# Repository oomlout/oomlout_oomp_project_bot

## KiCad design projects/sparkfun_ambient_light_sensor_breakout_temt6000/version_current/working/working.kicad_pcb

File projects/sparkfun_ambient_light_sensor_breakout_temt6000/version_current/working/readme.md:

# OOMP Project  
## Ambient_Light_Sensor_Breakout-TEMT6000  by sparkfun  
  
oomp key: oomp_projects_flat_sparkfun_ambient_light_sensor_breakout_temt6000  
(snippet of original readme)  
  
SparkFun Ambient Light Sensor Breakout Board - TEMT6000  
=========================================================  

[*SparkFun Ambient Light Sensor Breakout Board - TEMT6000 (BOB-08688)*](https://www.sparkfun.com/products/8688)  
  
 Basic breakout board for the TEMT6000 Ambient Light Sensor.  

Repository Contents  
-------------------  
  
* **/Hardware** - All Eagle design files (.brd, .sch)  
  
Documentation  
--------------  
  
* **[Hookup Guide](https://learn.sparkfun.com/tutorials/temt6000-ambient-light-sensor-hookup-guide)** - Basic hookup guide.  
  
License Information  
-------------------  
The hardware is released under [Creative Commons ShareAlike 4.0 International](https://creativecommons.org/licenses/by-sa/4.0/).  
  
Distributed as-is; no warranty is given.  
  
  full source readme at [readme_src.md](readme_src.md)  
  
source repo at: [https://github.com/sparkfun/Ambient_Light_Sensor_Breakout-TEMT6000](https://github.com/sparkfun/Ambient_Light_Sensor_Breakout-TEMT6000)  
## Board  

## Schematic  

[schematic pdf](working_schematic.pdf)  
## Images

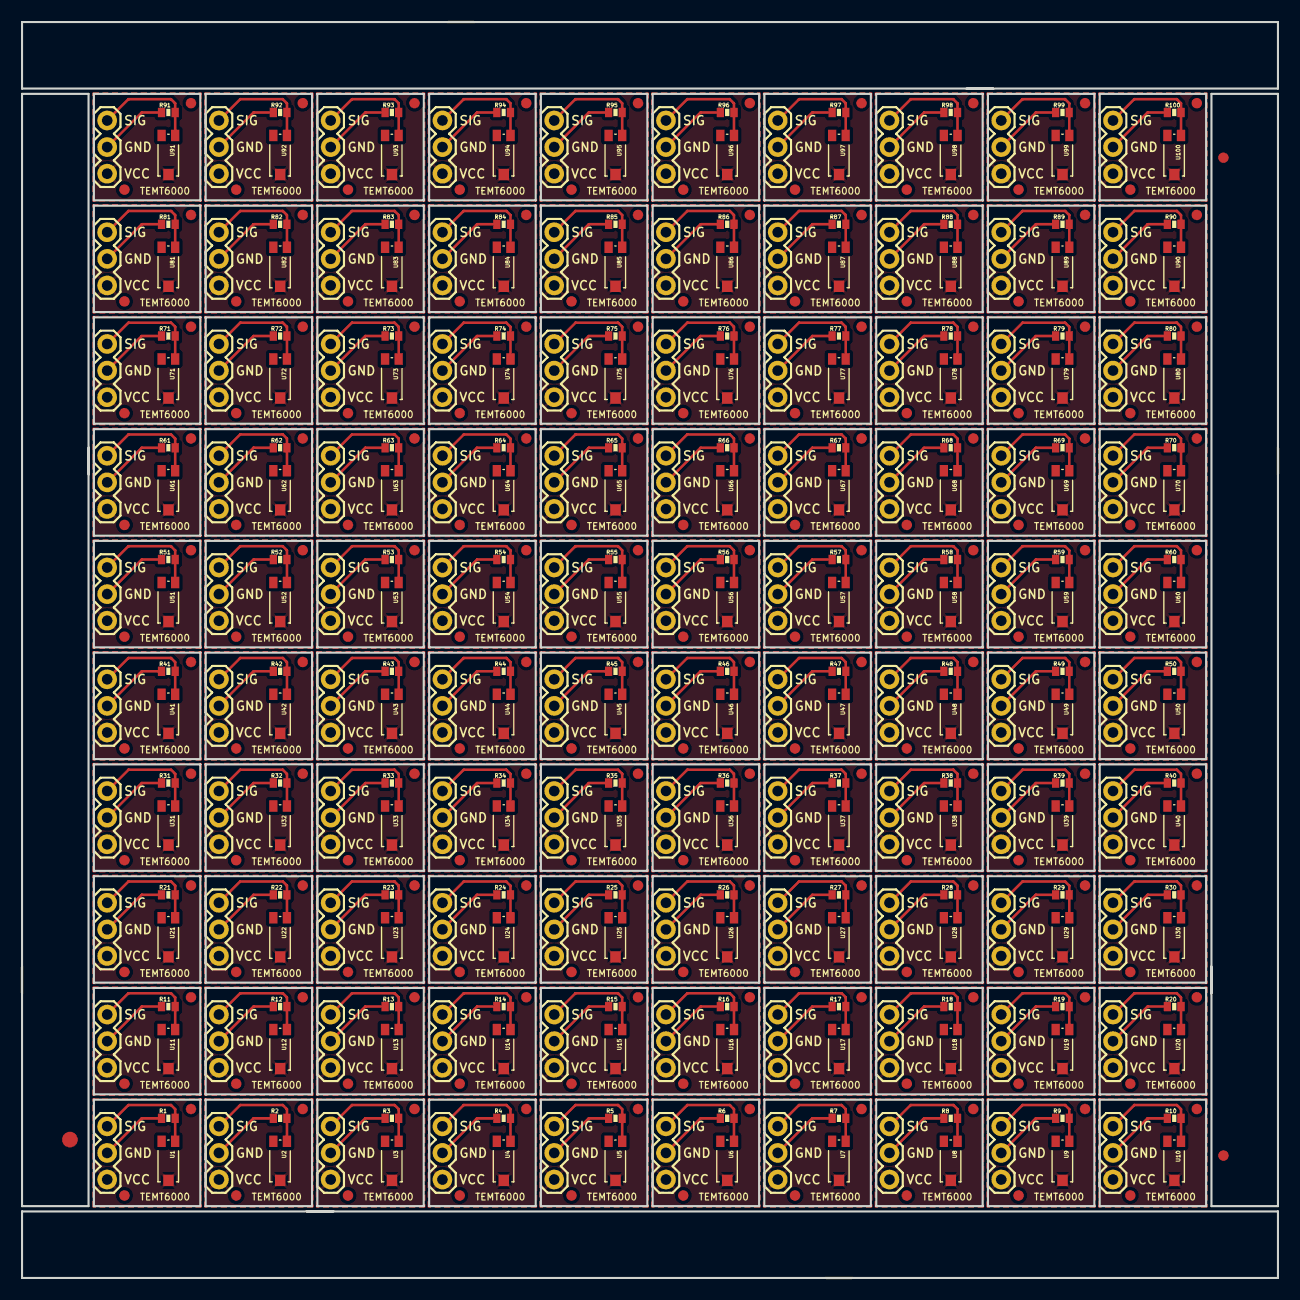
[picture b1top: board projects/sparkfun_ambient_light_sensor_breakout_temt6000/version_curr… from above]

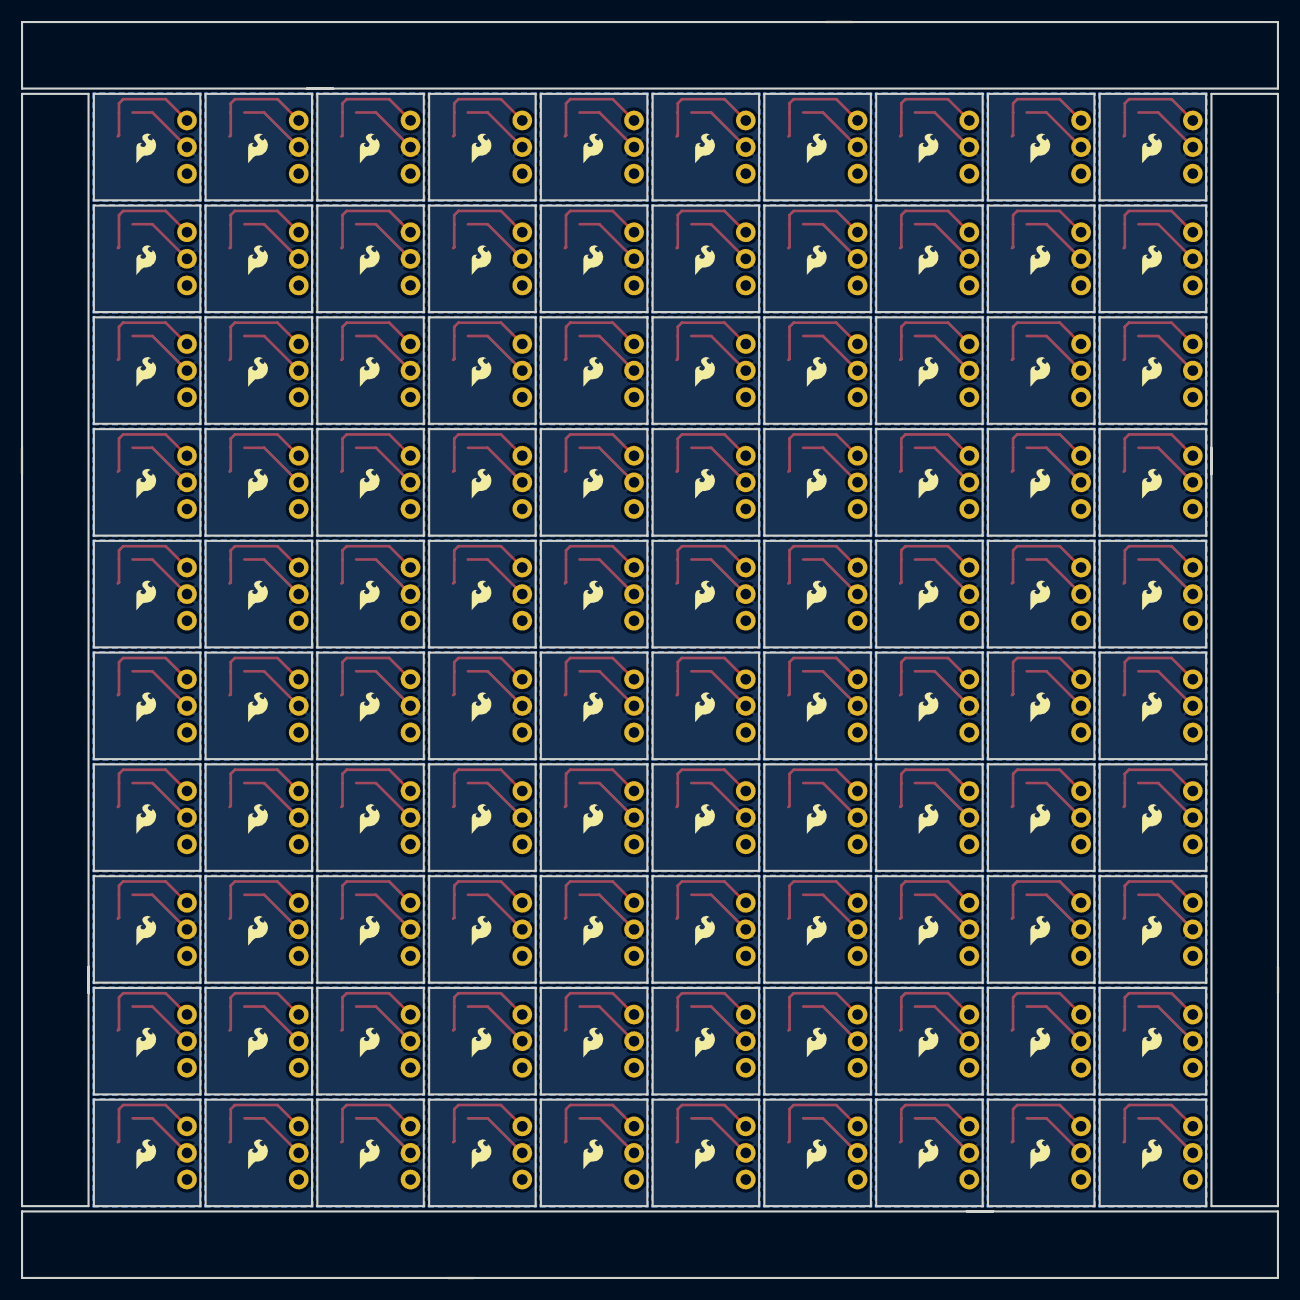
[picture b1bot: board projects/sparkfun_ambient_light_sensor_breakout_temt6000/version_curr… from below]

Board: 16 copper layers, 119.9 x 119.9 mm, 603 parts (100 on the bottom side), 300 nets.

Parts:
E$1, E$2, E$3, E$4, E$5, E$6, E$7, E$8, E$9, E$10, E$11, E$12, E$13, E$14, E$15, E$16, E$17, E$18, E$19, E$20, E$21, E$22, E$23, E$24, E$25, E$26, E$27, E$28, E$29, E$30, E$31, E$32, E$33, E$34, E$35, E$36, E$37, E$38, E$39, E$40, E$41, E$42, E$43, E$44, E$45, E$46, E$47, E$48, E$49, E$50, E$51, E$52, E$53, E$54, E$55, E$56, E$57, E$58, E$59, E$60, E$61, E$62, E$63, E$64, E$65, E$66, E$67, E$68, E$69, E$70, E$71, E$72, E$73, E$74, E$75, E$76, E$77, E$78, E$79, E$80, E$81, E$82, E$83, E$84, E$85, E$86, E$87, E$88, E$89, E$90, E$91, E$92, E$93, E$94, E$95, E$96, E$97, E$98, E$99, E$100, E$101, E$102, E$103, E$104, E$105, E$106, E$107, E$108, E$109, E$110, E$111, E$112, E$113, E$114, E$115, E$116, E$117, E$118, E$119, E$120, E$121, E$122, E$123, E$124, E$125, E$126, E$127, E$128, E$129, E$130, E$131, E$132, E$133, E$134, E$135, E$136, E$137, E$138, E$139, E$140, E$141, E$142, E$143, E$144, E$145, E$146, E$147, E$148, E$149, E$150, E$151, E$152, E$153, E$154, E$155, E$156, E$157, E$158, E$159, E$160, E$161, E$162, E$163, E$164, E$165, E$166, E$167, E$168, E$169, E$170, E$171, E$172, E$173, E$174, E$175, E$176, E$177, E$178, E$179, E$180, E$181, E$182, E$183, E$184, E$185, E$186, E$187, E$188, E$189, E$190, E$191, E$192, E$193, E$194, E$195, E$196, E$197, E$198, E$199, E$200, E$205, E$206: FIDUCIAL-1X2
E$201: FIDUCIAL-1.5X3
JP1, JP2, JP3, JP4, JP5, JP6, JP7, JP8, JP9, JP10, JP11, JP12, JP13, JP14, JP15, JP16, JP17, JP18, JP19, JP20, JP21, JP22, JP23, JP24, JP25, JP26, JP27, JP28, JP29, JP30, JP31, JP32, JP33, JP34, JP35, JP36, JP37, JP38, JP39, JP40, JP41, JP42, JP43, JP44, JP45, JP46, JP47, JP48, JP49, JP50, JP51, JP52, JP53, JP54, JP55, JP56, JP57, JP58, JP59, JP60, JP61, JP62, JP63, JP64, JP65, JP66, JP67, JP68, JP69, JP70, JP71, JP72, JP73, JP74, JP75, JP76, JP77, JP78, JP79, JP80, JP81, JP82, JP83, JP84, JP85, JP86, JP87, JP88, JP89, JP90, JP91, JP92, JP93, JP94, JP95, JP96, JP97, JP98, JP99, JP100: 1X03
R1, R2, R3, R4, R5, R6, R7, R8, R9, R10, R11, R12, R13, R14, R15, R16, R17, R18, R19, R20, R21, R22, R23, R24, R25, R26, R27, R28, R29, R30, R31, R32, R33, R34, R35, R36, R37, R38, R39, R40, R41, R42, R43, R44, R45, R46, R47, R48, R49, R50, R51, R52, R53, R54, R55, R56, R57, R58, R59, R60, R61, R62, R63, R64, R65, R66, R67, R68, R69, R70, R71, R72, R73, R74, R75, R76, R77, R78, R79, R80, R81, R82, R83, R84, R85, R86, R87, R88, R89, R90, R91, R92, R93, R94, R95, R96, R97, R98, R99, R100: 10K; 0402-RES
U1, U2, U3, U4, U5, U6, U7, U8, U9, U10, U11, U12, U13, U14, U15, U16, U17, U18, U19, U20, U21, U22, U23, U24, U25, U26, U27, U28, U29, U30, U31, U32, U33, U34, U35, U36, U37, U38, U39, U40, U41, U42, U43, U44, U45, U46, U47, U48, U49, U50, U51, U52, U53, U54, U55, U56, U57, U58, U59, U60, U61, U62, U63, U64, U65, U66, U67, U68, U69, U70, U71, U72, U73, U74, U75, U76, U77, U78, U79, U80, U81, U82, U83, U84, U85, U86, U87, U88, U89, U90, U91, U92, U93, U94, U95, U96, U97, U98, U99, U100: TEMT6000; TEMT6000-SEN
U$1, U$2, U$3, U$4, U$5, U$6, U$7, U$8, U$9, U$10, U$11, U$12, U$13, U$14, U$15, U$16, U$17, U$18, U$19, U$20, U$21, U$22, U$23, U$24, U$25, U$26, U$27, U$28, U$29, U$30, U$31, U$32, U$33, U$34, U$35, U$36, U$37, U$38, U$39, U$40, U$41, U$42, U$43, U$44, U$45, U$46, U$47, U$48, U$49, U$50, U$51, U$52, U$53, U$54, U$55, U$56, U$57, U$58, U$59, U$60, U$61, U$62, U$63, U$64, U$65, U$66, U$67, U$68, U$69, U$70, U$71, U$72, U$73, U$74, U$75, U$76, U$77, U$78, U$79, U$80, U$81, U$82, U$83, U$84, U$85, U$86, U$87, U$88, U$89, U$90, U$91, U$92, U$93, U$94, U$95, U$96, U$97, U$98, U$99, U$100: LOGO-SFESK; SFE-LOGO-FLAME

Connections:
GND: JP4.2, R1.1
GND1: JP1.2, R2.1
GND2: JP2.2, R3.1
GND3: JP3.2, R4.1
GND4: JP5.2, R5.1
GND5: JP6.2, R6.1
GND6: JP7.2, R7.1
GND7: JP8.2, R8.1
GND8: JP9.2, R9.1
GND9: JP10.2, R10.1
GND10: JP11.2, R11.1
GND11: JP12.2, R12.1
GND12: JP13.2, R13.1
GND13: JP14.2, R14.1
GND14: JP15.2, R15.1
GND15: JP16.2, R16.1
GND16: JP17.2, R17.1
GND17: JP18.2, R18.1
GND18: JP19.2, R19.1
GND19: JP20.2, R20.1
GND20: JP21.2, R21.1
GND21: JP22.2, R22.1
GND22: JP23.2, R23.1
GND23: JP24.2, R24.1
GND24: JP25.2, R25.1
GND25: JP26.2, R26.1
GND26: JP27.2, R27.1
GND27: JP28.2, R28.1
GND28: JP29.2, R29.1
GND29: JP30.2, R30.1
GND30: JP31.2, R31.1
GND31: JP32.2, R32.1
GND32: JP33.2, R33.1
GND33: JP34.2, R34.1
GND34: JP35.2, R35.1
GND35: JP36.2, R36.1
GND36: JP37.2, R37.1
GND37: JP38.2, R38.1
GND38: JP39.2, R39.1
GND39: JP40.2, R40.1
GND40: JP41.2, R41.1
GND41: JP42.2, R42.1
GND42: JP43.2, R43.1
GND43: JP44.2, R44.1
GND44: JP45.2, R45.1
GND45: JP46.2, R46.1
GND46: JP47.2, R47.1
GND47: JP48.2, R48.1
GND48: JP49.2, R49.1
GND49: JP50.2, R50.1
GND50: JP51.2, R51.1
GND51: JP52.2, R52.1
GND52: JP53.2, R53.1
GND53: JP54.2, R54.1
GND54: JP55.2, R55.1
GND55: JP56.2, R56.1
GND56: JP57.2, R57.1
GND57: JP58.2, R58.1
GND58: JP59.2, R59.1
GND59: JP60.2, R60.1
GND60: JP61.2, R61.1
GND61: JP62.2, R62.1
GND62: JP63.2, R63.1
GND63: JP64.2, R64.1
GND64: JP65.2, R65.1
GND65: JP66.2, R66.1
GND66: JP67.2, R67.1
GND67: JP68.2, R68.1
GND68: JP69.2, R69.1
GND69: JP70.2, R70.1
GND70: JP71.2, R71.1
GND71: JP72.2, R72.1
GND72: JP73.2, R73.1
GND73: JP74.2, R74.1
GND74: JP75.2, R75.1
GND75: JP76.2, R76.1
GND76: JP77.2, R77.1
GND77: JP78.2, R78.1
GND78: JP79.2, R79.1
GND79: JP80.2, R80.1
GND80: JP81.2, R81.1
GND81: JP82.2, R82.1
GND82: JP83.2, R83.1
GND83: JP84.2, R84.1
GND84: JP85.2, R85.1
GND85: JP86.2, R86.1
GND86: JP87.2, R87.1
GND87: JP88.2, R88.1
GND88: JP89.2, R89.1
GND89: JP90.2, R90.1
GND90: JP91.2, R91.1
GND91: JP92.2, R92.1
GND92: JP93.2, R93.1
GND93: JP94.2, R94.1
GND94: JP95.2, R95.1
GND95: JP96.2, R96.1
GND96: JP97.2, R97.1
GND97: JP98.2, R98.1
GND98: JP99.2, R99.1
GND99: JP100.2, R100.1
S: JP4.3, R1.2, U1.EMITTER
S1: JP1.3, R2.2, U2.EMITTER
S2: JP2.3, R3.2, U3.EMITTER
S3: JP3.3, R4.2, U4.EMITTER
S4: JP5.3, R5.2, U5.EMITTER
S5: JP6.3, R6.2, U6.EMITTER
S6: JP7.3, R7.2, U7.EMITTER
S7: JP8.3, R8.2, U8.EMITTER
S8: JP9.3, R9.2, U9.EMITTER
S9: JP10.3, R10.2, U10.EMITTER
S10: JP11.3, R11.2, U11.EMITTER
S11: JP12.3, R12.2, U12.EMITTER
S12: JP13.3, R13.2, U13.EMITTER
S13: JP14.3, R14.2, U14.EMITTER
S14: JP15.3, R15.2, U15.EMITTER
S15: JP16.3, R16.2, U16.EMITTER
S16: JP17.3, R17.2, U17.EMITTER
S17: JP18.3, R18.2, U18.EMITTER
S18: JP19.3, R19.2, U19.EMITTER
S19: JP20.3, R20.2, U20.EMITTER
S20: JP21.3, R21.2, U21.EMITTER
S21: JP22.3, R22.2, U22.EMITTER
S22: JP23.3, R23.2, U23.EMITTER
S23: JP24.3, R24.2, U24.EMITTER
S24: JP25.3, R25.2, U25.EMITTER
S25: JP26.3, R26.2, U26.EMITTER
S26: JP27.3, R27.2, U27.EMITTER
S27: JP28.3, R28.2, U28.EMITTER
S28: JP29.3, R29.2, U29.EMITTER
S29: JP30.3, R30.2, U30.EMITTER
S30: JP31.3, R31.2, U31.EMITTER
S31: JP32.3, R32.2, U32.EMITTER
S32: JP33.3, R33.2, U33.EMITTER
S33: JP34.3, R34.2, U34.EMITTER
S34: JP35.3, R35.2, U35.EMITTER
S35: JP36.3, R36.2, U36.EMITTER
S36: JP37.3, R37.2, U37.EMITTER
S37: JP38.3, R38.2, U38.EMITTER
S38: JP39.3, R39.2, U39.EMITTER
S39: JP40.3, R40.2, U40.EMITTER
S40: JP41.3, R41.2, U41.EMITTER
S41: JP42.3, R42.2, U42.EMITTER
S42: JP43.3, R43.2, U43.EMITTER
S43: JP44.3, R44.2, U44.EMITTER
S44: JP45.3, R45.2, U45.EMITTER
S45: JP46.3, R46.2, U46.EMITTER
S46: JP47.3, R47.2, U47.EMITTER
S47: JP48.3, R48.2, U48.EMITTER
S48: JP49.3, R49.2, U49.EMITTER
S49: JP50.3, R50.2, U50.EMITTER
S50: JP51.3, R51.2, U51.EMITTER
S51: JP52.3, R52.2, U52.EMITTER
S52: JP53.3, R53.2, U53.EMITTER
S53: JP54.3, R54.2, U54.EMITTER
S54: JP55.3, R55.2, U55.EMITTER
S55: JP56.3, R56.2, U56.EMITTER
S56: JP57.3, R57.2, U57.EMITTER
S57: JP58.3, R58.2, U58.EMITTER
S58: JP59.3, R59.2, U59.EMITTER
S59: JP60.3, R60.2, U60.EMITTER
S60: JP61.3, R61.2, U61.EMITTER
S61: JP62.3, R62.2, U62.EMITTER
S62: JP63.3, R63.2, U63.EMITTER
S63: JP64.3, R64.2, U64.EMITTER
S64: JP65.3, R65.2, U65.EMITTER
S65: JP66.3, R66.2, U66.EMITTER
S66: JP67.3, R67.2, U67.EMITTER
S67: JP68.3, R68.2, U68.EMITTER
S68: JP69.3, R69.2, U69.EMITTER
S69: JP70.3, R70.2, U70.EMITTER
S70: JP71.3, R71.2, U71.EMITTER
S71: JP72.3, R72.2, U72.EMITTER
S72: JP73.3, R73.2, U73.EMITTER
S73: JP74.3, R74.2, U74.EMITTER
S74: JP75.3, R75.2, U75.EMITTER
S75: JP76.3, R76.2, U76.EMITTER
S76: JP77.3, R77.2, U77.EMITTER
S77: JP78.3, R78.2, U78.EMITTER
S78: JP79.3, R79.2, U79.EMITTER
S79: JP80.3, R80.2, U80.EMITTER
S80: JP81.3, R81.2, U81.EMITTER
S81: JP82.3, R82.2, U82.EMITTER
S82: JP83.3, R83.2, U83.EMITTER
S83: JP84.3, R84.2, U84.EMITTER
S84: JP85.3, R85.2, U85.EMITTER
S85: JP86.3, R86.2, U86.EMITTER
S86: JP87.3, R87.2, U87.EMITTER
S87: JP88.3, R88.2, U88.EMITTER
S88: JP89.3, R89.2, U89.EMITTER
S89: JP90.3, R90.2, U90.EMITTER
S90: JP91.3, R91.2, U91.EMITTER
S91: JP92.3, R92.2, U92.EMITTER
S92: JP93.3, R93.2, U93.EMITTER
S93: JP94.3, R94.2, U94.EMITTER
S94: JP95.3, R95.2, U95.EMITTER
S95: JP96.3, R96.2, U96.EMITTER
S96: JP97.3, R97.2, U97.EMITTER
S97: JP98.3, R98.2, U98.EMITTER
S98: JP99.3, R99.2, U99.EMITTER
S99: JP100.3, R100.2, U100.EMITTER
VCC: JP4.1, U1.COLLECTOR
VCC1: JP1.1, U2.COLLECTOR
VCC2: JP2.1, U3.COLLECTOR
VCC3: JP3.1, U4.COLLECTOR
VCC4: JP5.1, U5.COLLECTOR
VCC5: JP6.1, U6.COLLECTOR
VCC6: JP7.1, U7.COLLECTOR
VCC7: JP8.1, U8.COLLECTOR
VCC8: JP9.1, U9.COLLECTOR
VCC9: JP10.1, U10.COLLECTOR
VCC10: JP11.1, U11.COLLECTOR
VCC11: JP12.1, U12.COLLECTOR
VCC12: JP13.1, U13.COLLECTOR
VCC13: JP14.1, U14.COLLECTOR
VCC14: JP15.1, U15.COLLECTOR
VCC15: JP16.1, U16.COLLECTOR
VCC16: JP17.1, U17.COLLECTOR
VCC17: JP18.1, U18.COLLECTOR
VCC18: JP19.1, U19.COLLECTOR
VCC19: JP20.1, U20.COLLECTOR
VCC20: JP21.1, U21.COLLECTOR
VCC21: JP22.1, U22.COLLECTOR
VCC22: JP23.1, U23.COLLECTOR
VCC23: JP24.1, U24.COLLECTOR
VCC24: JP25.1, U25.COLLECTOR
VCC25: JP26.1, U26.COLLECTOR
VCC26: JP27.1, U27.COLLECTOR
VCC27: JP28.1, U28.COLLECTOR
VCC28: JP29.1, U29.COLLECTOR
VCC29: JP30.1, U30.COLLECTOR
VCC30: JP31.1, U31.COLLECTOR
VCC31: JP32.1, U32.COLLECTOR
VCC32: JP33.1, U33.COLLECTOR
VCC33: JP34.1, U34.COLLECTOR
VCC34: JP35.1, U35.COLLECTOR
VCC35: JP36.1, U36.COLLECTOR
VCC36: JP37.1, U37.COLLECTOR
VCC37: JP38.1, U38.COLLECTOR
VCC38: JP39.1, U39.COLLECTOR
VCC39: JP40.1, U40.COLLECTOR
VCC40: JP41.1, U41.COLLECTOR
VCC41: JP42.1, U42.COLLECTOR
VCC42: JP43.1, U43.COLLECTOR
VCC43: JP44.1, U44.COLLECTOR
VCC44: JP45.1, U45.COLLECTOR
VCC45: JP46.1, U46.COLLECTOR
VCC46: JP47.1, U47.COLLECTOR
VCC47: JP48.1, U48.COLLECTOR
VCC48: JP49.1, U49.COLLECTOR
VCC49: JP50.1, U50.COLLECTOR
VCC50: JP51.1, U51.COLLECTOR
VCC51: JP52.1, U52.COLLECTOR
VCC52: JP53.1, U53.COLLECTOR
VCC53: JP54.1, U54.COLLECTOR
VCC54: JP55.1, U55.COLLECTOR
VCC55: JP56.1, U56.COLLECTOR
VCC56: JP57.1, U57.COLLECTOR
VCC57: JP58.1, U58.COLLECTOR
VCC58: JP59.1, U59.COLLECTOR
VCC59: JP60.1, U60.COLLECTOR
VCC60: JP61.1, U61.COLLECTOR
VCC61: JP62.1, U62.COLLECTOR
VCC62: JP63.1, U63.COLLECTOR
VCC63: JP64.1, U64.COLLECTOR
VCC64: JP65.1, U65.COLLECTOR
VCC65: JP66.1, U66.COLLECTOR
VCC66: JP67.1, U67.COLLECTOR
VCC67: JP68.1, U68.COLLECTOR
VCC68: JP69.1, U69.COLLECTOR
VCC69: JP70.1, U70.COLLECTOR
VCC70: JP71.1, U71.COLLECTOR
VCC71: JP72.1, U72.COLLECTOR
VCC72: JP73.1, U73.COLLECTOR
VCC73: JP74.1, U74.COLLECTOR
VCC74: JP75.1, U75.COLLECTOR
VCC75: JP76.1, U76.COLLECTOR
VCC76: JP77.1, U77.COLLECTOR
VCC77: JP78.1, U78.COLLECTOR
VCC78: JP79.1, U79.COLLECTOR
VCC79: JP80.1, U80.COLLECTOR
VCC80: JP81.1, U81.COLLECTOR
VCC81: JP82.1, U82.COLLECTOR
VCC82: JP83.1, U83.COLLECTOR
VCC83: JP84.1, U84.COLLECTOR
VCC84: JP85.1, U85.COLLECTOR
VCC85: JP86.1, U86.COLLECTOR
VCC86: JP87.1, U87.COLLECTOR
VCC87: JP88.1, U88.COLLECTOR
VCC88: JP89.1, U89.COLLECTOR
VCC89: JP90.1, U90.COLLECTOR
VCC90: JP91.1, U91.COLLECTOR
VCC91: JP92.1, U92.COLLECTOR
VCC92: JP93.1, U93.COLLECTOR
VCC93: JP94.1, U94.COLLECTOR
VCC94: JP95.1, U95.COLLECTOR
VCC95: JP96.1, U96.COLLECTOR
VCC96: JP97.1, U97.COLLECTOR
VCC97: JP98.1, U98.COLLECTOR
VCC98: JP99.1, U99.COLLECTOR
VCC99: JP100.1, U100.COLLECTOR

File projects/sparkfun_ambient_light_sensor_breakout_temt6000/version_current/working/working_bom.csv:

Row,Description,Part,References,Value,Footprint,Quantity Per PCB,Status,Datasheet
1,,M03PTH,JP4,M03PTH,1X03,1, ,
2,,RESISTOR0402-RES,R1,10K,0402-RES,1, ,
3,,TEMT6000,U1,TEMT6000,TEMT6000-SEN,1, ,
4,,LOGO-SFESK,U$1,LOGO-SFESK,SFE-LOGO-FLAME,1, ,





Project info:
Schematic:,working
Variant:,default
Revision:,
Date:,2023-08-06_12-55-58
KiCad Version:,7.0.6-7.0.6~ubuntu22.04.1
Statistics:
Component Groups:,4
Component Count:,4 (0 SMD/ 0 THT)
Fitted Components:,4 (0 SMD/ 0 THT)
Number of PCBs:,1
Total Components:,4

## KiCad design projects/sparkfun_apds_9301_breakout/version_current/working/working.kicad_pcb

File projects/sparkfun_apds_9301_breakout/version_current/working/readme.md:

# OOMP Project  
## APDS-9301_Breakout  by sparkfun  
  
oomp key: oomp_projects_flat_sparkfun_apds_9301_breakout  
(snippet of original readme)  
  
SparkFun APDS-9301 Lux Sensor Breakout  
======================================  

[*APDS-9301 Lux Sensor Breakout (SEN-14350)*](https://www.sparkfun.com/products/14350)  
  
The APDS-9301 Lux Sensor Breakout is a small I<sup>2</sup>C based sensor with dynamic range.   
  
Repository Contents  
-------------------  
* **/Hardware** - All Eagle design files (.brd, .sch)  
* **/Libraries** - All Arduino libraries and board examples  
* **/Production** - Test bed files and production panel files  

Documentation  
--------------  
* **[Library](https://github.com/sparkfun/SparkFun_APDS9301_Library)** - Arduino library for the APDs-9301.  
* **[Hookup Guide](https://learn.sparkfun.com/tutorials/apds-9301-sensor-hookup-guide)** - Basic hookup guide for the APDS-9301 Breakout Board.  
  
License Information  
-------------------  
  
This product is _**open source**_!   
  
Please review the LICENSE.md file for license information.   
  
If you have any questions or concerns on licensing, please contact techsupport@sparkfun.com.  
  
Distributed as-is; no warranty is given.  
  
- Your friends at SparkFun.  
  
  full source readme at [readme_src.md](readme_src.md)  
  
source repo at: [https://github.com/sparkfun/APDS-9301_Breakout](https://github.com/sparkfun/APDS-9301_Breakout)  
## Board  

## Schematic  

[schematic pdf](working_schematic.pdf)  
## Images

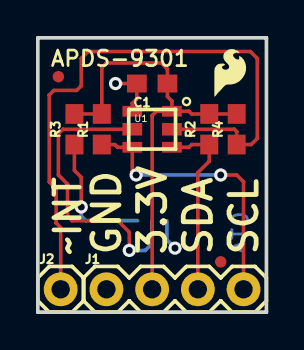
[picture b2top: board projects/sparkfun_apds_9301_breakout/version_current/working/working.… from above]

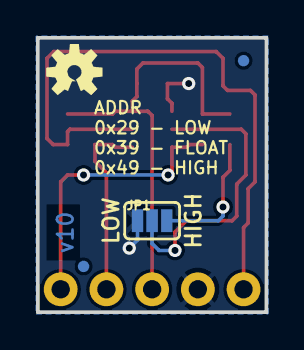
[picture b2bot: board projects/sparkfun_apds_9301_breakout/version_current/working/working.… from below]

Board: 4 copper layers, 12.7 x 15.2 mm, 16 parts (4 on the bottom side), 7 nets.

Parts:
C1: 0.1uF; 0603
FD1, FD2, FD3, FD4: FIDUCIALUFIDUCIAL; FIDUCIAL-MICRO
FRAME1: FRAME-LETTER; CREATIVE_COMMONS
J1: 1X04
J2: 1X01
JP1: JUMPER-SMT_3_NO_SILK; SMT-JUMPER_3_NO_SILK
LOGO1: SFE_LOGO_FLAME.1_INCH; SFE_LOGO_FLAME_.1
LOGO2: OSHW-LOGOS; OSHW-LOGO-S
R1, R2: 4.7k; 0603
R3, R4: 10k; 0603
U1: APDS-9301; CHIPLED-6

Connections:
ADDR: JP1.2, U1.P3
GND: C1.2, J1.1, JP1.1, U1.P2
INT: J2.1, R4.1, U1.P6
unnamed: JP1.3, R3.1
SCL: J1.4, R1.1, U1.P4
SDA: J1.3, R2.1, U1.P5
VCC: C1.1, J1.2, R1.2, R2.2, R3.2, R4.2, U1.P1

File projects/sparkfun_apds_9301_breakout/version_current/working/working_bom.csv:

Row,Description,Part,References,Value,Footprint,Quantity Per PCB,Status,Datasheet
1,,0.1UF-0603-25V-5%,C1,0.1UF-0603-25V-5%,0603,1, ,
2,,FRAME-LETTER,FRAME1,FRAME-LETTER,CREATIVE_COMMONS,1, ,
3,,CONN_01,J2,CONN_01,1X01,1, ,
4,,I2C_STANDARD,J1,I2C_STANDARD,1X04,1, ,
5,,JUMPER-SMT_3_NO_SILK,JP1,JUMPER-SMT_3_NO_SILK,SMT-JUMPER_3_NO_SILK,1, ,
6,,OSHW-LOGOS,LOGO2,OSHW-LOGOS,OSHW-LOGO-S,1, ,
7,,SFE_LOGO_FLAME.1_INCH,LOGO1,SFE_LOGO_FLAME.1_INCH,SFE_LOGO_FLAME_.1,1, ,
8,,10KOHM-0603-1/10W-1%,R3 R4,10KOHM-0603-1/10W-1%,0603,2, ,
9,,4.7KOHM-0603-1/10W-1%,R1 R2,4.7KOHM-0603-1/10W-1%,0603,2, ,
10,,APDS-9301,U1,APDS-9301,CHIPLED-6,1, ,





Project info:
Schematic:,working
Variant:,default
Revision:,
Date:,2023-08-06_12-55-58
KiCad Version:,7.0.6-7.0.6~ubuntu22.04.1
Statistics:
Component Groups:,10
Component Count:,12 (0 SMD/ 0 THT)
Fitted Components:,12 (0 SMD/ 0 THT)
Number of PCBs:,1
Total Components:,12

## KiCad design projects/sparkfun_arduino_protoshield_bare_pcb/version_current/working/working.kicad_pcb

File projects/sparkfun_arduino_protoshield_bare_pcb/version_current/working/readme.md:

# Arduino_ProtoShield_Bare_PCB by sparkfun  
This is a harvested standardized copy of a project from github.  
The original project can be found at:  
https://github.com/sparkfun/Arduino_ProtoShield_Bare_PCB  
Please consult that link for additional, details, files, and license information.  
Note: It was auto harvested and if the original repo had more than one board file or anything out of the ordinary the files here are likely not representative.

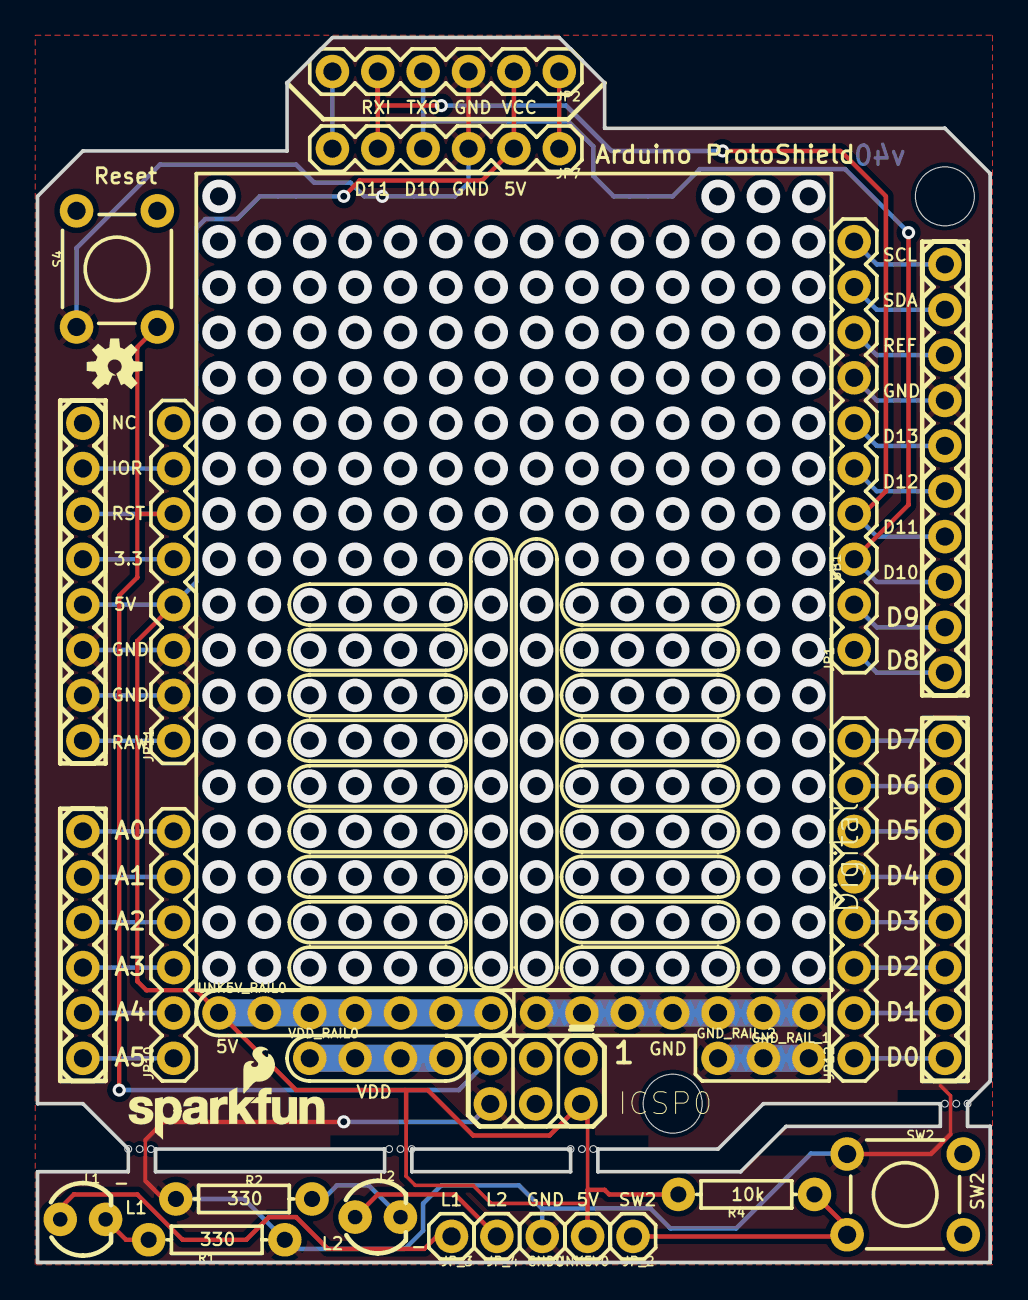
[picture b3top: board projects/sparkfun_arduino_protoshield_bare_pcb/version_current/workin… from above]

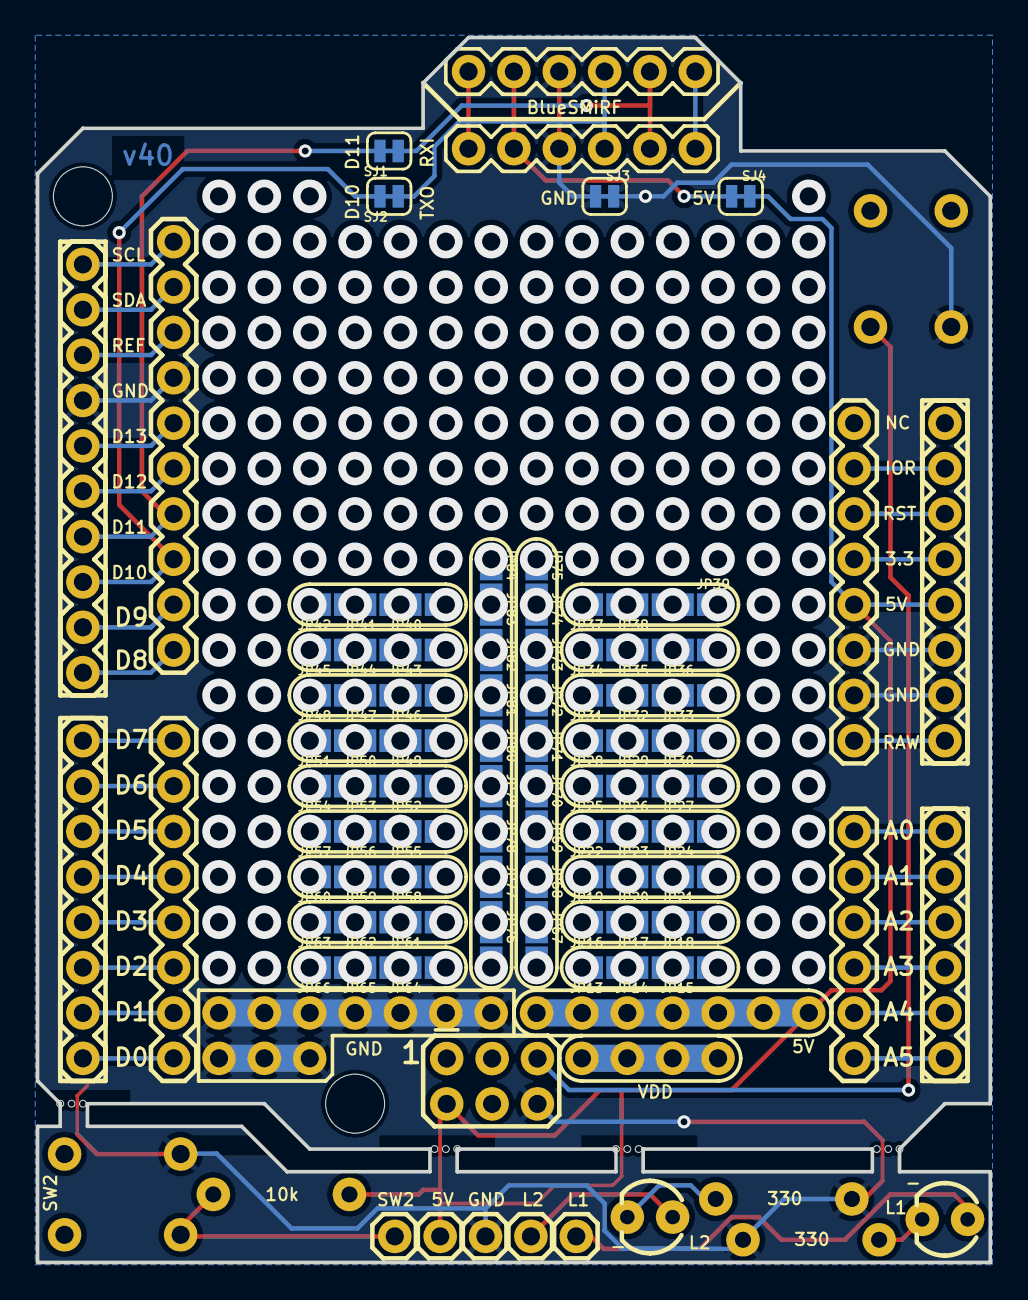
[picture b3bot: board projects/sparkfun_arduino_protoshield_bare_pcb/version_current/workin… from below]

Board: 2 copper layers, 53.3 x 68.6 mm, 115 parts (76 on the bottom side), 40 nets.

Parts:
@HOLE0, @HOLE1, @HOLE2, @HOLE3, @HOLE4, @HOLE5, @HOLE6, @HOLE7, @HOLE8, @HOLE9, @HOLE10, @HOLE11: (no value)
BB1: BREADBOARDMINI; BREADBOARD-MINI
GND0: 1X01
GND_RAIL_1: 1X07_NO_SILK
GND_RAIL_2: 1X03_NO_SILK
ICSP0: ICSP; 2X3
JP1: 1X10
JP2: BlueSMiRF; 1X06
JP7, JP10: 1X06
JP8: ARDUINO_R3_SHIELDR3_PROTO_SHIELD; UNO_R3_PROTO_SHIELD
JP11, JP12: 1X08
JP13, JP14, JP15: D_RAIL1; SMT-JUMPER_2_NO_NO-SILK
JP16, JP17, JP18: D_RAIL2; SMT-JUMPER_2_NO_NO-SILK
JP19, JP20, JP21: D_RAIL3; SMT-JUMPER_2_NO_NO-SILK
JP22, JP23, JP24: D_RAIL4; SMT-JUMPER_2_NO_NO-SILK
JP25, JP26, JP27: D_RAIL5; SMT-JUMPER_2_NO_NO-SILK
JP28, JP29, JP30: D_RAIL6; SMT-JUMPER_2_NO_NO-SILK
JP31, JP32, JP33: D_RAIL7; SMT-JUMPER_2_NO_NO-SILK
JP34, JP35, JP36: D_RAIL8; SMT-JUMPER_2_NO_NO-SILK
JP37, JP38, JP39: D_RAIL9; SMT-JUMPER_2_NO_NO-SILK
JP40, JP41, JP42, JP43, JP44, JP45, JP46, JP47, JP48: D_RAIL18; SMT-JUMPER_2_NO_NO-SILK
JP49, JP50, JP51: D_RAIL17; SMT-JUMPER_2_NO_NO-SILK
JP52, JP53, JP54: D_RAIL16; SMT-JUMPER_2_NO_NO-SILK
JP55, JP56, JP57: D_RAIL15; SMT-JUMPER_2_NO_NO-SILK
JP58, JP59, JP60: D_RAIL14; SMT-JUMPER_2_NO_NO-SILK
JP61, JP62, JP63: D_RAIL13; SMT-JUMPER_2_NO_NO-SILK
JP64, JP65, JP66: D_RAIL12; SMT-JUMPER_2_NO_NO-SILK
JP67, JP68, JP69, JP70, JP71, JP72, JP73, JP74, JP75: D_RAIL10; SMT-JUMPER_2_NO_NO-SILK
JP76, JP77, JP78, JP79, JP80, JP81, JP82, JP83, JP84: D_RAIL11; SMT-JUMPER_2_NO_NO-SILK
JP_2, JP_3, JP_4: 1X01
L1, L2: LED_3MM
LOGO1: OSHW-LOGOS; OSHW-LOGO-S
R1, R2: 330; AXIAL-0.3
R4: 10k; AXIAL-0.3
S4: MOMENTARY-SWITCH-SPST-PTH-6.0MM; TACTILE_SWITCH_PTH_6.0MM
SJ1, SJ2, SJ3, SJ4: JUMPER-SMT_2_NC_TRACE_SILK; SMT-JUMPER_2_NC_TRACE_SILK
SW2: MOMENTARY-SWITCH-SPST-PTH-6.0MM; TACTILE_SWITCH_PTH_6.0MM
U$1: SFE_LOGO_NAME_FLAME.1_INCH; SFE_LOGO_NAME_FLAME_.1
UNK5V0: 1X01
UNK5V_RAIL0: 1X07_NO_SILK
VDD_RAIL0: 1X04_NO_SILK

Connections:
3.3: JP8.3.3V, JP11.5
5V: ICSP0.2, JP8.5V, JP11.4, R4.P$2, SJ4.2, UNK5V0.1, UNK5V_RAIL0.1, UNK5V_RAIL0.2, UNK5V_RAIL0.3, UNK5V_RAIL0.4, UNK5V_RAIL0.5, UNK5V_RAIL0.6, UNK5V_RAIL0.7
A1: JP8.A1, JP10.5
A2: JP8.A2, JP10.4
A5: JP8.A5, JP10.1
AREF: JP1.8, JP8.AREF
D2: JP8.D2, JP12.3
D2_NC: JP_2.1, R4.P$1, SW2.3
D3: JP8.D3, JP12.4
D4: JP8.D4, JP12.5
D5: JP8.D5, JP12.6
D6: JP8.D6, JP12.7
D7: JP8.D7, JP12.8
D8: JP1.1, JP8.D8
D9: JP1.2, JP8.D9
D10: JP1.3, JP8.D10, SJ2.2
D11: JP1.4, JP8.D11, SJ1.2
D12: JP1.5, JP8.D12
D13: JP1.6, JP8.D13
GND: GND0.1, GND_RAIL_1.1, GND_RAIL_1.2, GND_RAIL_1.3, GND_RAIL_1.4, GND_RAIL_1.5, GND_RAIL_1.6, GND_RAIL_1.7, GND_RAIL_2.1, GND_RAIL_2.2, GND_RAIL_2.3, ICSP0.6, JP1.7, JP2.3, JP7.3, JP8.GND@0, JP8.GND@1, JP8.GND@2, JP11.2, JP11.3, R1.P$1, R2.P$1, S4.1, SJ3.1, SJ3.2, SW2.1
JP3: JP_3.1, L1.A
JP4: JP_4.1, L2.A
unnamed: JP8.IOREF, JP11.7
unnamed: JP8.A0, JP10.6
unnamed: JP8.A4, JP10.2
unnamed: JP8.A3, JP10.3
unnamed: L1.K, R1.P$2
unnamed: L2.K, R2.P$2
NC1: JP2.1, JP7.1
NC2: JP2.6, JP7.6
RESET: ICSP0.5, JP8.RES, JP11.6, S4.3
RX: JP8.RX, JP12.1
RX-I: JP2.5, JP7.5, SJ1.1
SCL: JP1.10, JP8.SCL
SDA: JP1.9, JP8.SDA
TX: JP8.TX, JP12.2
TX-O: JP2.4, JP7.4, SJ2.1
VCC: JP2.2, JP7.2, SJ4.1
VDD: VDD_RAIL0.1, VDD_RAIL0.2, VDD_RAIL0.3, VDD_RAIL0.4
VIN: JP8.VIN, JP11.1

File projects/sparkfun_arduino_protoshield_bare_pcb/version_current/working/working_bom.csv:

"Id";"Designator";"Footprint";"Quantity";"Designation";"Supplier and ref";
1;"UNK5V_RAIL0,GND_RAIL_1";"1X07_NO_SILK";2;"";;;
2;"@HOLE4,@HOLE1,@HOLE0,@HOLE5,@HOLE10,@HOLE11,@HOLE7,@HOLE8,@HOLE6,@HOLE2,@HOLE3,@HOLE9";"";12;"";;;
3;"JP_2,GND0,JP_3,JP_4,UNK5V0";"1X01";5;"";;;
4;"LOGO1";"OSHW-LOGO-S";1;"OSHW-LOGOS";;;
5;"U$1";"SFE_LOGO_NAME_FLAME_.1";1;"SFE_LOGO_NAME_FLAME.1_INCH";;;
6;"JP8";"UNO_R3_PROTO_SHIELD";1;"ARDUINO_R3_SHIELDR3_PROTO_SHIELD";;;
7;"L1,L2";"LED_3MM";2;"";;;
8;"SW2,S4";"TACTILE_SWITCH_PTH_6.0MM";2;"MOMENTARY-SWITCH-SPST-PTH-6.0MM";;;
9;"R4";"AXIAL-0.3";1;"10k";;;
10;"GND_RAIL_2";"1X03_NO_SILK";1;"";;;
11;"R1,R2";"AXIAL-0.3";2;"330";;;
12;"JP10,JP7";"1X06";2;"";;;
13;"JP11,JP12";"1X08";2;"";;;
14;"BB1";"BREADBOARD-MINI";1;"BREADBOARDMINI";;;
15;"JP1";"1X10";1;"";;;
16;"VDD_RAIL0";"1X04_NO_SILK";1;"";;;
17;"JP2";"1X06";1;"BlueSMiRF";;;
18;"ICSP0";"2X3";1;"ICSP";;;
19;"JP42,JP44,JP46,JP48,JP40,JP45,JP47,JP43,JP41";"SMT-JUMPER_2_NO_NO-SILK";9;"D_RAIL18";;;
20;"JP37,JP39,JP38";"SMT-JUMPER_2_NO_NO-SILK";3;"D_RAIL9";;;
21;"JP56,JP55,JP57";"SMT-JUMPER_2_NO_NO-SILK";3;"D_RAIL15";;;
22;"JP20,JP21,JP19";"SMT-JUMPER_2_NO_NO-SILK";3;"D_RAIL3";;;
23;"SJ3,SJ1,SJ4,SJ2";"SMT-JUMPER_2_NC_TRACE_SILK";4;"JUMPER-SMT_2_NC_TRACE_SILK";;;
24;"JP32,JP33,JP31";"SMT-JUMPER_2_NO_NO-SILK";3;"D_RAIL7";;;
25;"JP34,JP36,JP35";"SMT-JUMPER_2_NO_NO-SILK";3;"D_RAIL8";;;
26;"JP79,JP77,JP82,JP78,JP80,JP83,JP76,JP81,JP84";"SMT-JUMPER_2_NO_NO-SILK";9;"D_RAIL11";;;
27;"JP59,JP58,JP60";"SMT-JUMPER_2_NO_NO-SILK";3;"D_RAIL14";;;
28;"JP49,JP51,JP50";"SMT-JUMPER_2_NO_NO-SILK";3;"D_RAIL17";;;
29;"JP53,JP52,JP54";"SMT-JUMPER_2_NO_NO-SILK";3;"D_RAIL16";;;
30;"JP29,JP30,JP28";"SMT-JUMPER_2_NO_NO-SILK";3;"D_RAIL6";;;
31;"JP69,JP72,JP67,JP70,JP75,JP71,JP74,JP73,JP68";"SMT-JUMPER_2_NO_NO-SILK";9;"D_RAIL10";;;
32;"JP18,JP16,JP17";"SMT-JUMPER_2_NO_NO-SILK";3;"D_RAIL2";;;
33;"JP26,JP25,JP27";"SMT-JUMPER_2_NO_NO-SILK";3;"D_RAIL5";;;
34;"JP66,JP64,JP65";"SMT-JUMPER_2_NO_NO-SILK";3;"D_RAIL12";;;
35;"JP22,JP23,JP24";"SMT-JUMPER_2_NO_NO-SILK";3;"D_RAIL4";;;
36;"JP14,JP15,JP13";"SMT-JUMPER_2_NO_NO-SILK";3;"D_RAIL1";;;
37;"JP63,JP61,JP62";"SMT-JUMPER_2_NO_NO-SILK";3;"D_RAIL13";;;

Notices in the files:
projects/sparkfun_apds_9301_breakout/version_current/working/working.kicad_sch:
Released under the Creative Commons
projects/sparkfun_atmega128rfa1_dev/version_current/working/working.kicad_sch:
http://creativecommons.org/licenses/by-sa/3.0
parts and their libraries:
Released under the Creative Commons Attribution Share-Alike 4.0 License
